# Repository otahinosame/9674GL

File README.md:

# 9674GL
GL516 Case Compatible Keyboard
GL516ケース対応キーボード

9674GL keyboard a.k.a. wagatatami
9674GL、またの名を「我が畳」。

hash tag: #9674GL

## コンセプト

* 40%キーボード感覚で使える65%キーボード。
* 96キーレイアウトを65%サイズ（キー数は74キー）に凝縮。

* 右端の5行3列のエリアは、数字入力のためのテンキー、レイヤーを使わないカーソル移動のためのナビゲーションクラスタ、40%配列に納まりきらない記号類など、様々な用途に合わせて自由に使える。
* 気分や作業内容によってキーキャップとキーマップを取り替えることで、かゆいところに手が届く自分だけの相棒になります。

## 配列のこだわり

* 分割スペースバーとその両サイドを左右対象にすることで、親指を起点とした操作がしやすい配列。
* 右下最下段を1uキー5個にすることで、好きな位置にアローキーを配置できる。
* キーキャップはよくあるBaseキットでだいたい揃うので、キーキャップの選択肢が豊富。（2uが3個必要なのと、Enterキーが1.25uなのでキーキャップの選択時は要注意）

## ビルドガイド

サリチル酸さん著の共通ビルドガイドを参考に組み立ててください。

GL516 互換PCB共通ビルドガイド
https://zenn.dev/salicylic_acid3/books/gl516_build_guide

### キットの内容物

| 項目                               | 数量 |
| ---------------------------------- | ---- |
| PCB (ダイオード、ソケット実装済み) | 1    |
| スイッチプレート                   | 1    |
| ピンソケット                       | 2    |

### キット以外で必要なもの

| 項目                                                         | 数量 |
| ------------------------------------------------------------ | ---- |
| GL516ケースと付属品一式 | 1    |
| Pro Micro | 1|
| ピンヘッダ |2 |
| MX互換スイッチ                                               | 74   |
| MX互換キーキャッップ                           | 74   |
| MX互換スタビライザー（2u）                                   | 3    |

### コンスルー同梱版の組み立て方

ピンヘッダの代わりに、コンスルーをPro Microにはんだ付けします。
* コンスルーをPCBに差し込みます
* コンスルーの反対側にPro Microを差し込みます
* Pro Microとコンスルーをはんだ付けします

### デコレーションプレート

BOOTHで購入いただくと、デコレーションプレートのカットデータがダウンロードできます。
また、遊舎工房のアクリルカットサービスに登録される予定のGL516汎用デコレーションプレートを注文することもできます。

## 入手先

BOOTHにて販売予定です。
https://otahinosame.booth.pm/items/3636926

## 謝辞

サリチル酸さん（ https://github.com/Salicylic-acid3 ）には、テンプレートの提供、設計データのレビュー、製造・頒布のサポートなど全面的に開発を助けていただきました。ありがとうございます。

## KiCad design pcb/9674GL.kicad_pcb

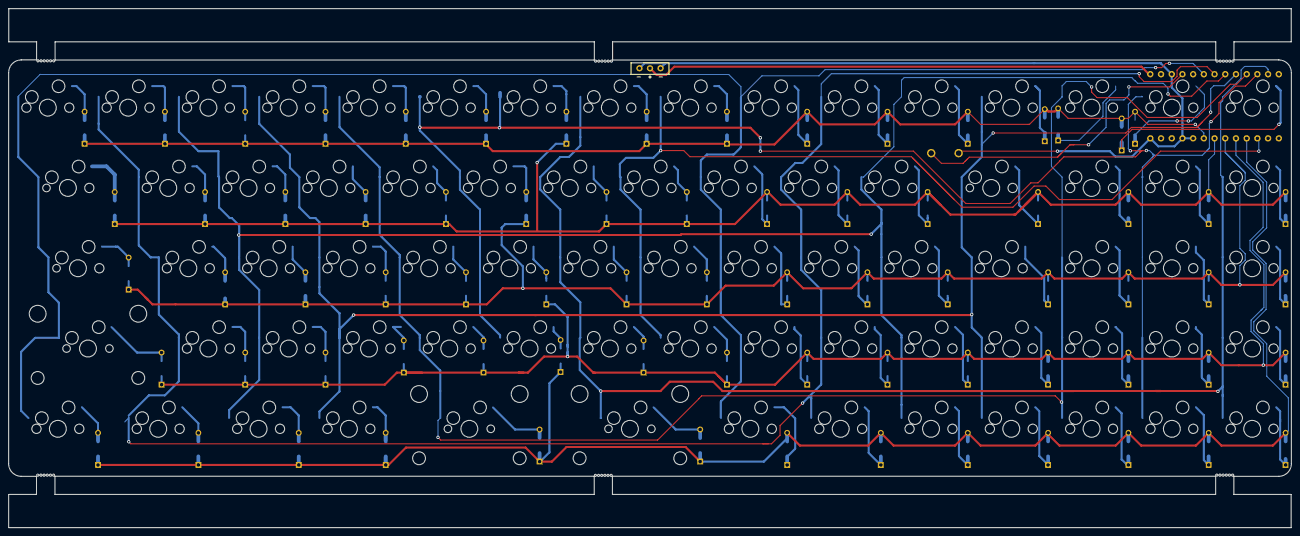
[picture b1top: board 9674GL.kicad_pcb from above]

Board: 2 copper layers, 304.4 x 123.1 mm, 157 parts (1 on the bottom side), 90 nets.

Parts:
D1, D2, D3, D4, D5, D6, D7, D8, D9, D10, D11, D12, D13, D14, D15, D16, D17, D18, D19, D20, D21, D22, D23, D24, D25, D26, D27, D28, D29, D30, D31, D32, D33, D34, D35, D36, D37, D38, D39, D40, D41, D42, D43, D44, D45, D46, D47, D48, D49, D50, D51, D52, D53, D54, D55, D56, D57, D58, D59, D60, D61, D62, D63, D64, D65, D66, D67, D68, D69, D70, D71, D72, D73, D74: D; Diode_TH_SMD
J1: Conn_01x02; Battery_XH2.5_GL_PCB
Ref**: Val**; Mouse_Bite_Hole
Ref**#2, Ref**#3, Ref**#4, Ref**#5, Ref**#6: Val**; Mouse_Bite_Hole
SW1, SW6, SW7, SW8, SW9, SW11, SW12, SW13, SW14, SW16, SW17, SW18, SW19, SW20, SW21, SW22, SW23, SW24, SW26, SW27, SW28, SW29, SW30, SW31, SW32, SW33, SW34, SW36, SW37, SW38, SW39, SW40, SW41, SW42, SW43, SW44, SW45, SW46, SW47, SW48, SW50, SW51, SW52, SW53, SW54, SW55, SW58, SW59, SW60, SW61, SW62, SW63, SW64, SW66, SW67, SW68, SW69, SW71, SW72, SW73, SW74: SW_PUSH; CherryMX_Hotswap_1.0u
SW2, SW56: SW_PUSH; CherryMX_Hotswap_1.5u
SW3: SW_PUSH; CherryMX_Hotswap_1.75u
SW4, SW25, SW35: SW_PUSH; CherryMX_Hotswap_2u_Rev
SW5, SW10, SW15, SW49, SW57: SW_PUSH; CherryMX_Hotswap_1.25u
SW65, SW70: SW_PUSH; CherryMX_Hotswap_1.0u_Small1
SW80: SW_PUSH; ResetSW
U1: BLEMicroPro; Micon_BMP_GL

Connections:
Bat+: J1.1, U1.25
Col0: SW1.1, SW2.1, SW3.1, SW4.1, SW5.1, SW40.1, SW41.1, SW42.1, SW43.1, SW44.1, U1.20
Col1: SW6.1, SW7.1, SW8.1, SW9.1, SW10.1, SW45.1, SW46.1, SW47.1, SW48.1, SW49.1, U1.19
Col2: SW11.1, SW12.1, SW13.1, SW14.1, SW15.1, SW50.1, SW51.1, SW52.1, SW53.1, SW54.1, U1.18
Col3: SW16.1, SW17.1, SW18.1, SW19.1, SW20.1, SW55.1, SW56.1, SW57.1, SW58.1, SW59.1, U1.17
Col4: SW21.1, SW22.1, SW23.1, SW24.1, SW25.1, SW60.1, SW61.1, SW62.1, SW63.1, SW64.1, U1.16
Col5: SW26.1, SW27.1, SW28.1, SW29.1, SW30.1, SW65.1, SW66.1, SW67.1, SW68.1, SW69.1, U1.15
Col6: SW31.1, SW32.1, SW33.1, SW34.1, SW35.1, SW70.1, SW71.1, SW72.1, SW73.1, SW74.1, U1.14
Col7: SW36.1, SW37.1, SW38.1, SW39.1, U1.10
GND: J1.2, SW80.2, U1.3, U1.4, U1.23, U1.26
unnamed: D1.2, SW1.2
unnamed: D2.2, SW2.2
unnamed: D3.2, SW3.2
unnamed: D4.2, SW4.2
unnamed: D5.2, SW5.2
unnamed: D6.2, SW6.2
unnamed: D7.2, SW7.2
unnamed: D8.2, SW8.2
unnamed: D9.2, SW9.2
unnamed: D10.2, SW10.2
unnamed: D11.2, SW11.2
unnamed: D12.2, SW12.2
unnamed: D13.2, SW13.2
unnamed: D14.2, SW14.2
unnamed: D15.2, SW15.2
unnamed: D16.2, SW16.2
unnamed: D17.2, SW17.2
unnamed: D18.2, SW18.2
unnamed: D19.2, SW19.2
unnamed: D20.2, SW20.2
unnamed: D21.2, SW21.2
unnamed: D22.2, SW22.2
unnamed: D23.2, SW23.2
unnamed: D24.2, SW24.2
unnamed: D25.2, SW25.2
unnamed: D26.2, SW26.2
unnamed: D27.2, SW27.2
unnamed: D28.2, SW28.2
unnamed: D29.2, SW29.2
unnamed: D30.2, SW30.2
unnamed: D31.2, SW31.2
unnamed: D32.2, SW32.2
unnamed: D33.2, SW33.2
unnamed: D34.2, SW34.2
unnamed: D35.2, SW35.2
unnamed: D36.2, SW36.2
unnamed: D37.2, SW37.2
unnamed: D38.2, SW38.2
unnamed: D39.2, SW39.2
unnamed: D40.1, SW40.2
unnamed: D41.1, SW41.2
unnamed: D42.1, SW42.2
unnamed: D43.1, SW43.2
unnamed: D44.1, SW44.2
unnamed: D45.1, SW45.2
unnamed: D46.1, SW46.2
unnamed: D47.1, SW47.2
unnamed: D48.1, SW48.2
unnamed: D49.1, SW49.2
unnamed: D50.1, SW50.2
unnamed: D51.1, SW51.2
unnamed: D52.1, SW52.2
unnamed: D53.1, SW53.2
unnamed: D54.1, SW54.2
unnamed: D55.1, SW55.2
unnamed: D56.1, SW56.2
unnamed: D57.1, SW57.2
unnamed: D58.1, SW58.2
unnamed: D59.1, SW59.2
unnamed: D60.1, SW60.2
unnamed: D61.1, SW61.2
unnamed: D62.1, SW62.2
unnamed: D63.1, SW63.2
unnamed: D64.1, SW64.2
unnamed: D65.1, SW65.2
unnamed: D66.1, SW66.2
unnamed: D67.1, SW67.2
unnamed: D68.1, SW68.2
unnamed: D69.1, SW69.2
unnamed: D70.1, SW70.2
unnamed: D71.1, SW71.2
unnamed: D72.1, SW72.2
unnamed: D73.1, SW73.2
unnamed: D74.1, SW74.2
Reset: SW80.1, U1.22
Row0: D1.1, D6.1, D11.1, D16.1, D21.1, D26.1, D31.1, D36.1, D40.2, D45.2, D50.2, D55.2, D60.2, D65.2, D70.2, U1.5
Row1: D2.1, D7.1, D12.1, D17.1, D22.1, D27.1, D32.1, D37.1, D41.2, D46.2, D51.2, D56.2, D61.2, D66.2, D71.2, U1.6
Row2: D3.1, D8.1, D13.1, D18.1, D23.1, D28.1, D33.1, D38.1, D42.2, D47.2, D52.2, D57.2, D62.2, D67.2, D72.2, U1.7
Row3: D4.1, D9.1, D14.1, D19.1, D24.1, D29.1, D34.1, D39.1, D43.2, D48.2, D53.2, D58.2, D63.2, D68.2, D73.2, U1.8
Row4: D5.1, D10.1, D15.1, D20.1, D25.1, D30.1, D35.1, D44.2, D49.2, D54.2, D59.2, D64.2, D69.2, D74.2, U1.9

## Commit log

2021-12-29 add qmk firmware
2022-02-12 disable via lighting
2022-02-27 Create gl516_9674gl_config.json
    This reverts commit 3a53e0b074fdb60cab956f90d1db3b49e285e56a.
2022-03-23 add non-auto shift hex
2022-07-13 Create LICENSE
2022-07-13 Create pcb
2022-07-13 update license
2022-07-13 add pcb and plate
2023-09-22 remove keymap_jp keycodes from default keymap
2023-09-22 add vial keymap and vial hex
